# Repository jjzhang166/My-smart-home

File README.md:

# 目录结构说明

***

## server

服务器端程序(主要在Ubuntu12.04上测试, linux平台编译，运行都是没问题的)

使用方法请参考[编译和安装](http://git.oschina.net/xmeter/My-smart-home/wikis/%E7%BC%96%E8%AF%91%E5%92%8C%E5%AE%89%E8%A3%85)

友情提示go语言服务器版本请移步

http://git.oschina.net/ckrissun/smarthome-server

## dserver
 下一版开发的重点，服务器端由集中式变为分布式架构。
 
## tools 

提供些由于网络问题不好或者政策原因，软件包及调试工具

## opencv/facedect

人脸检测的源代码及例子(基于opencv + haar)

##  FastDFS

提供分布式云存储服务 ，感谢 Happy Fish / YuQing 的辛勤劳动

更多详细信息：http://www.csource.org/ 或者 googlecode有此项目

## iOS_Client、Android_Client、FirefoxOS_Client

各平台的客户端

* iOS客户端使用xcode5或以上打开即可

* Andriod客户端使用eclipse打开即可

 假如没有android开发环境， 可直接下载[已编译的Apk](http://git.oschina.net/xmeter/My-smart-home/blob/Client/Android_Client/bin/MyNode.apk)

* FirefoxOS客户端使用除记事本外的文本编辑器打开即可

**PS:现在客户端相关移至Client分支，确认无误后合并至master**

## ClientAPI、ClientWeb、ServerAPI、ServerWeb

http服务器代码，有问题请[提交Issue](http://git.oschina.net/xmeter/My-smart-home/issues/new)

**PS:现在Web相关移至Server分支，确认无误后合并至master**

## webhook

代码自动部署，持续集成

## hardware

硬件ardunio以及相关传感器的demo。(LM35，MQ2 MQ7 , W5100等)
     
* [硬件介绍](http://git.oschina.net/xmeter/My-smart-home/wikis/%E7%A1%AC%E4%BB%B6%E9%83%A8%E5%88%86%E4%BB%8B%E7%BB%8D)
       
***

> 更详细的说明，请移步 [WiKi](http://git.oschina.net/xmeter/My-smart-home/wikis/Home)

> 希望有新的小伙伴加入！

# 联系方式

***

### [李子](git.oschina.net/xmeter) liyongming1982@163.com _管理员_

服务器、硬件、Android Client

### [Rex](http://git.oschina.net/ckrissun) ckrissun@gmail.com _管理员_

服务器、协议、硬件

### [泷涯](http://git.oschina.net/sy) 896640547@qq.com _管理员_

数据库、Web、API
 
### [Pajoke](http://git.oschina.net/hell-prototypes) pajoke@163.com

硬件

更多Pajoke介绍请移步 ：  http://www.hellprototypes.com

### [siz](http://git.oschina.net/aliyuns) siz@sonwa.cn

iOS Client

### [fireman](http://git.oschina.net/colma) david_lxh@aliyun.com

特别感谢fireman，把Web服务移植到树莓派 (并写下文档供后来者参考)

### [Raythan](http://git.oschina.net/Raythan) raythandong@gmail.com

硬件

### [孤鹰](http://git.oschina.net/604217454) 604217454@qq.com

iOS Client

### [mzer](http://git.oschina.net/liduanjun) liduanjun@126.com

硬件及Web

# 感谢

***

   * 感谢xiangjm资助我200元人民币购买3D打印机
   * 感谢我老婆这个月多给了我点零花钱
   * 感谢3D淘宝店老板便宜了50元钱 http://3dprinter-diy.taobao.com/?spm=2013.1.0.0.donECP
   * ......

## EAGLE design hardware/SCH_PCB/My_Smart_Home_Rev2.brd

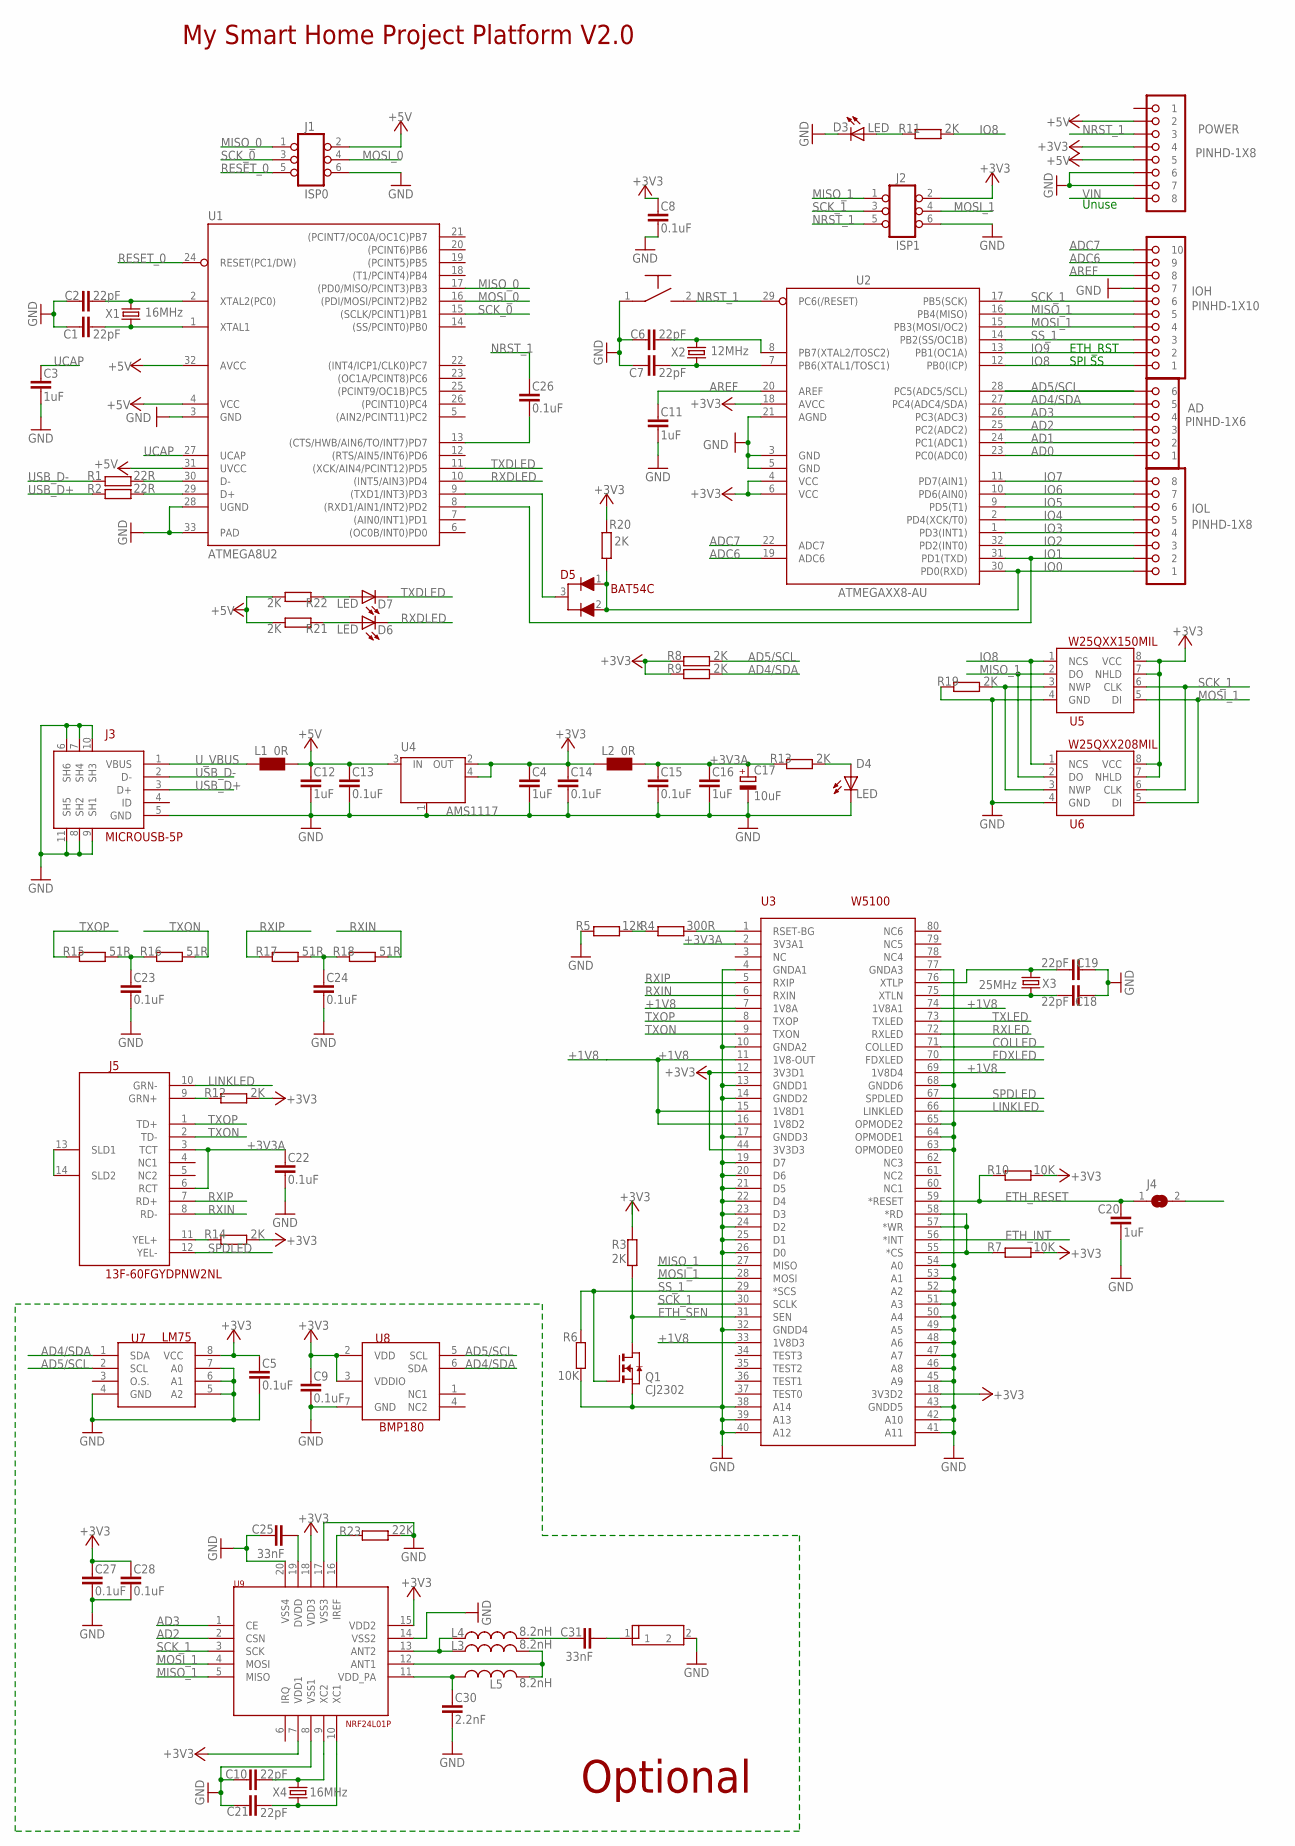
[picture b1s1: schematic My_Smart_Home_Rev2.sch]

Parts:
AD: PINHD-1X6; 1X06
ANT1: 2.4G_ANT1; 2.4G_PCB_ANT
C1, C2, C6, C7, C10, C18, C19, C21: 22pF; C0603
C3, C4, C11, C12, C16, C20: 1uF; C0603
C5, C8, C9, C13, C14, C15, C22, C23, C24, C26, C27, C28: 0.1uF; C0603
C17: 10uF; C0805
C25, C31: 33nF; C0603
C30: 2.2nF; C0603
D3, D4, D6, D7: LED; LED0805
D5: BAT54C; SOT23
IOH: PINHD-1X10; 1X10
IOL: PINHD-1X8; 1X08
J1: ISP0; 2X03
J2: ISP1; 2X03
J3: MICROUSB-5P; MICROUSB-5P-SMD
J4: JUMPER; SOLDER_JUMPER
J5: 13F-60FGYDPNW2NL
L1, L2: 0R; R0603
L3, L4, L5: 8.2nH; R0603
POWER: PINHD-1X8; 1X08
Q1: CJ2302; SOT23
R1, R2: 22R; R0603
R3, R8, R9, R11, R12, R13, R14, R19, R20, R21, R22: 2K; R0603
R4: 300R; R0603
R5: 12K; R0603
R6, R7, R10: 10K; R0603
R15, R16, R17, R18: 51R; R0603
R23: 22K; R0603
SW2: SW-2; SW-2P-SMD
U1: ATMEGA8U2; MLF32
U2: ATMEGAXX8-AU; TQFP32-08
U3: W5100; SQFP-S-10X10-80
U4: AMS1117; SOT223
U5: W25QXX150MIL; 8S1
U6: W25QXX208MIL; 8S2
U7: LM75; 8S1
U8: BMP180; LGA-7P
U9: NRF24L01P; QFN20
X1, X4: 16MHz; HC49UP
X2: 12MHz; HC49UP
X3: 25MHz; HC49UP

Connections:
+1V8: U3.7 (1V8A), U3.11 (1V8-OUT), U3.15 (1V8D1), U3.16 (1V8D2), U3.33 (1V8D3), U3.69 (1V8D4), U3.74 (1V8A1)
+3V3: C4.2, C5.2, C8.2, C9.2, C14.2, C27.2, C28.2, J2.2, L2.1, POWER.4, R3.2, R7.2, R8.2, R9.2, R10.2, R12.1, R14.1, R20.2, U2.4 (VCC), U2.6 (VCC), U2.18 (AVCC), U3.12 (3V3D1), U3.18 (3V3D2), U3.44 (3V3D3), U4.2 (OUT), U4.4 (OUT), U5.7 (NHLD), U5.8 (VCC), U6.7 (NHLD), U6.8 (VCC), U7.8 (VCC), U8.2 (VDD), U8.3 (VDDIO), U9.7 (VDD1), U9.15 (VDD2), U9.18 (VDD3)
+3V3A: C15.2, C16.2, C17.1 (+), C22.2, J5.3 (TCT), J5.6 (RCT), L2.2, R13.2, U3.2 (3V3A1)
+5V: C12.2, C13.2, J1.2, L1.2, POWER.2, POWER.5, R21.1, R22.1, U1.4 (VCC), U1.31 (UVCC), U1.32 (AVCC), U4.3 (IN)
AD0: AD.1, U2.23 (PC0(ADC0))
AD1: AD.2, U2.24 (PC1(ADC1))
AD2: AD.3, U2.25 (PC2(ADC2)), U9.2 (CSN)
AD3: AD.4, U2.26 (PC3(ADC3)), U9.1 (CE)
AD4/SDA: AD.5, R9.1, U2.27 (PC4(ADC4/SDA)), U7.1 (SDA), U8.6 (SDA)
AD5/SCL: AD.6, R8.1, U2.28 (PC5(ADC5/SCL)), U7.2 (SCL), U8.5 (SCL)
ADC6: IOH.9, U2.19 (ADC6)
ADC7: IOH.10, U2.22 (ADC7)
AREF: C11.2, IOH.8, U2.20 (AREF)
COLLED: U3.71 (COLLED)
ETH_INT: U3.56 (*INT)
ETH_RESET: C20.2, J4.1, R10.1, U3.59 (*RESET)
ETH_SEN: Q1.3 (D), R3.1, U3.31 (SEN)
FDXLED: U3.70 (FDXLED)
GND: ANT1.2, C1.1, C2.1, C3.1, C4.1, C5.1, C6.1, C7.1, C8.1, C9.1, C10.1, C11.1, C12.1, C13.1, C14.1, C15.1, C16.1, C17.2 (-), C18.1, C19.1, C20.1, C21.1, C22.1, C23.1, C24.1, C25.2, C27.1, C28.1, C30.1, D3.C, D4.C, IOH.7, J1.6, J2.6, J3.5 (GND), J3.6 (SH6), J3.7 (SH4), J3.8 (SH2), J3.9 (SH1), J3.10 (SH3), J3.11 (SH5), POWER.6, POWER.7, Q1.2 (S), R5.1, R6.1, R19.2, R23.1, SW2.1, U1.3 (GND), U1.28 (UGND), U1.33 (PAD), U2.3 (GND), U2.5 (GND), U2.21 (AGND), U3.4 (GNDA1), U3.10 (GNDA2), U3.13 (GNDD1), U3.14 (GNDD2), U3.17 (GNDD3), U3.19 (D7), U3.20 (D6), U3.21 (D5), U3.22 (D4), U3.23 (D3), U3.24 (D2), U3.25 (D1), U3.26 (D0), U3.32 (GNDD4), U3.38 (A14), U3.39 (A13), U3.40 (A12), U3.41 (A11), U3.42 (A10), U3.43 (GNDD5), U3.45 (A9), U3.46 (A8), U3.47 (A7), U3.48 (A6), U3.49 (A5), U3.50 (A4), U3.51 (A3), U3.52 (A2), U3.53 (A1), U3.54 (A0), U3.63 (OPMODE0), U3.64 (OPMODE1), U3.65 (OPMODE2), U3.68 (GNDD6), U3.77 (GNDA3), U4.1 (GND/ADJ), U5.4 (GND), U6.4 (GND), U7.4 (GND), U7.5 (A2), U7.6 (A1), U7.7 (A0), U8.7 (GND), U9.8 (VSS1), U9.14 (VSS2), U9.17 (VSS3), U9.20 (VSS4)
IO0: D5.1, D5.2, IOL.1, R20.1, U2.30 (PD0(RXD))
IO1: IOL.2, U1.8 ((RXD1/AIN1/INT2)PD2), U2.31 (PD1(TXD))
IO2: IOL.3, U2.32 (PD2(INT0))
IO3: IOL.4, U2.1 (PD3(INT1))
IO4: IOL.5, U2.2 (PD4(XCK/T0))
IO5: IOL.6, U2.9 (PD5(T1))
IO6: IOL.7, U2.10 (PD6(AIN0))
IO7: IOL.8, U2.11 (PD7(AIN1))
IO8: IOH.1, R11.1, U2.12 (PB0(ICP)), U5.1 (NCS), U6.1 (NCS)
IO9: IOH.2, J4.2, U2.13 (PB1(OC1A))
LINKLED: J5.10 (GRN-), U3.66 (LINKLED)
MISO_0: J1.1, U1.17 ((PD0/MISO/PCINT3)PB3)
MISO_1: IOH.5, J2.1, U2.16 (PB4(MISO)), U3.27 (MISO), U5.2 (DO), U6.2 (DO), U9.5 (MISO)
MOSI_0: J1.4, U1.16 ((PDI/MOSI/PCINT2)PB2)
MOSI_1: IOH.4, J2.4, U2.15 (PB3(MOSI/OC2)), U3.28 (MOSI), U5.5 (DI), U6.5 (DI), U9.4 (MOSI)
unnamed: C2.2, U1.2 (XTAL2(PC0)), X1.2
unnamed: C1.2, U1.1 (XTAL1), X1.1
unnamed: C18.2, U3.75 (XTLN), X3.2
unnamed: R7.1, U3.55 (*CS), U3.57 (*WR), U3.58 (*RD)
unnamed: C19.2, U3.76 (XTLP), X3.1
unnamed: C10.2, U9.9 (XC2), X4.2
unnamed: D5.3, U1.9 ((TXD1/INT3)PD3)
unnamed: C26.1, U1.13 ((CTS/HWB/AIN6/TO/INT7)PD7)
unnamed: R1.2, U1.30 (D-)
unnamed: D7.A, R22.2
unnamed: R2.2, U1.29 (D+)
unnamed: C21.2, U9.10 (XC1), X4.1
unnamed: L3.1, L4.1, U9.13 (ANT2)
unnamed: D4.A, R13.1
unnamed: D3.A, R11.2
unnamed: C6.2, U2.8 (PB7(XTAL2/TOSC2)), X2.2
unnamed: C7.2, U2.7 (PB6(XTAL1/TOSC1)), X2.1
unnamed: R4.2, U3.1 (RSET-BG)
unnamed: R4.1, R5.2
unnamed: J5.11 (YEL+), R14.2
unnamed: J5.9 (GRN+), R12.2
unnamed: C23.2, R15.1, R16.2
unnamed: D6.A, R21.2
unnamed: R23.2, U9.16 (IREF)
unnamed: J5.13 (SLD1), J5.14 (SLD2)
unnamed: C25.1, U9.19 (DVDD)
unnamed: C24.2, R17.1, R18.2
unnamed: L3.2, L5.2, U9.12 (ANT1)
unnamed: C30.2, L5.1, U9.11 (VDD_PA)
unnamed: R19.1, U5.3 (NWP), U6.3 (NWP)
unnamed: ANT1.1, C31.1
unnamed: C31.2, L4.2
NRST_1: C26.2, J2.5, POWER.3, SW2.2, U2.29 (PC6(/RESET))
RESET_0: J1.5, U1.24 (RESET(PC1/DW))
RXDLED: D6.C, U1.10 ((INT5/AIN3)PD4)
RXIN: J5.8 (RD-), R18.1, U3.6 (RXIN)
RXIP: J5.7 (RD+), R17.2, U3.5 (RXIP)
RXLED: U3.72 (RXLED)
SCK_0: J1.3, U1.15 ((SCLK/PCINT1)PB1)
SCK_1: IOH.6, J2.3, U2.17 (PB5(SCK)), U3.30 (SCLK), U5.6 (CLK), U6.6 (CLK), U9.3 (SCK)
SPDLED: J5.12 (YEL-), U3.67 (SPDLED)
SS_1: IOH.3, Q1.1 (G), R6.2, U2.14 (PB2(SS/OC1B)), U3.29 (*SCS)
TXDLED: D7.C, U1.11 ((XCK/AIN4/PCINT12)PD5)
TXLED: U3.73 (TXLED)
TXON: J5.2 (TD-), R16.1, U3.9 (TXON)
TXOP: J5.1 (TD+), R15.2, U3.8 (TXOP)
UCAP: C3.2, U1.27 (UCAP)
USB_D+: J3.3 (D+), R2.1
USB_D-: J3.2 (D-), R1.1
U_VBUS: J3.1 (VBUS), L1.1
VIN: POWER.8

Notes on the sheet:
Unuse
SPI SS
ETH_RST
My Smart Home Project Platform V2.0
Optional

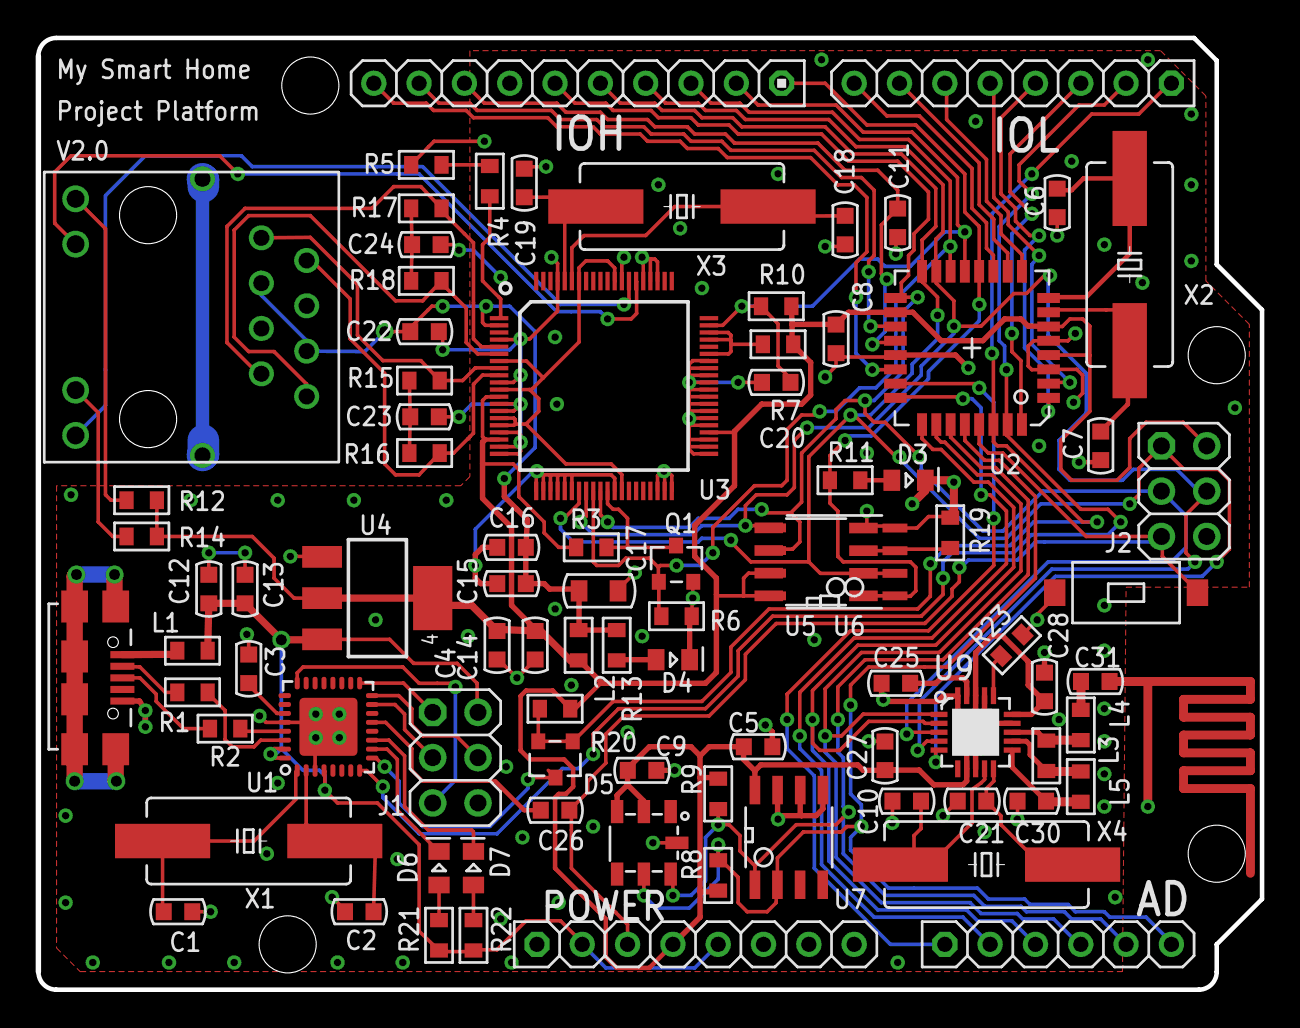
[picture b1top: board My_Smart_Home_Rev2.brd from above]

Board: 2 copper layers, 68.6 x 53.3 mm, 88 parts (1 on the bottom side), 79 nets.

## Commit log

2014-05-02 first version of my smart home server
2014-05-02 first version of android client
2014-05-02 add some debug or test scritp (python shell or php)
2014-05-02 first version of www (web) ,test it ie and firefox
2014-05-02 add readme
2014-05-03 add wiki link
2014-05-08 添加服务器端说明
2014-05-18 添加硬件介绍链接
2014-05-21 added mydebug, redislog instead of printf, added heartbeat and so on
2014-05-21 android client new protocol ,added light activity , add heart beat
2014-05-21 added some file
2014-05-21 hardware added MQ2 MQ7 sensor demo
2014-05-21 add hardware demo descript
2014-05-21 add second version of android client and server for compiler error
2014-05-21 added more file for server
2014-05-23 added light control demo wiht w5100
2014-05-29 Added .gitignore
2014-05-29 脚本移动
2014-05-29 dynamic add user , added server start script
2014-05-29 added two test development user in script
2014-05-29 mysql.php error
2014-05-31 添加小伙伴的邮箱
2014-06-01 removed *.o files improved chat send handling
2014-06-01 New iOS Project
2014-06-01 added chat message limitation to 70 length
2014-06-01 added iphone client development siz
2014-06-01 增加小伙伴
2014-06-02 added webhook
2014-06-03 add register feature , and modified some script
2014-06-03 change mode 777 for stop.sh
2014-06-03 change server port to 6379
2014-06-03 added log level for server crash
2014-06-03 added fake node client for test
2014-06-04 添加小伙伴
2014-06-05 欢迎小伙伴，掌声在哪里
2014-06-05 enable heart beat , and the value is 120s
2014-06-06 changed tcp-keepalive to 60s
2014-06-06 added debug info for heart beat
2014-06-06 for heart beat
2014-06-06 for avoid invalid client
2014-06-06 a socket cant login twice
2014-06-06 just for test
2014-06-07 fix webhook error
2014-06-07 fix tcp keepalive
2014-06-07 use heart beat , and delete redis native timeout
2014-06-07 show login fail reason
2014-06-07 put last android client MyNode.apk in bin
2014-06-07 修改android client 说明
2014-06-13 improved server compiling script
2014-06-13 fix server Makefile install error
2014-06-14 removed unused redis-related uitls
2014-06-18 added polarssl-havege algorithm library for register random generator
2014-06-18 fix havege library missing file && add test example
2014-06-19 added havege library compiling
2014-06-26 fix Broadcast Receiver leak
2014-06-26 support speech recognize
2014-06-28 添加感谢
2014-07-01 support on to air update
2014-07-01 fix ota bug check version.txt
2014-07-08 added restful api for first version use beego and go language
2014-07-08 added go beego gomysqldriver tools for restful api
2014-07-08 added restful
2014-07-08 go support 64 os
2014-07-09 show login status
2014-07-09 update version number for online update
2014-07-09 update android client apk
2014-07-09 changed go project structure
2014-07-11 restful: don't always open/close mysql db
2014-07-11 added models module
2014-07-13 close rows to free sql connection && write http header when errors issued.
2014-07-14 add restful tools
2014-07-16 added a company host page
2014-07-19 modified some ui , and fix some socket issue etc
2014-07-21 add a wizard for new user , and fixed online update bug ,etc
2014-07-29 added light activity , color pick ,time date pick etc
2014-08-01 add ipod style wheel
2014-08-02 我只是改了一下README.md
2014-08-02 把自己加进了小伙伴名单里
2014-08-02 热烈欢迎泷涯到来
2014-08-02 好吧我多打了个s
2014-08-02 将web分支的内容提交至主分支
2014-08-02 放这么大的东西不好 = =
2014-08-02 美化了一下README.md
2014-08-02 README.md
2014-08-04 项目的发展是大家努力贡献的结构 * 项目的首页出现大家的联系方式，是我们自己对自己的一个肯定
2014-08-04 tools 说明
2014-08-05 开源协议更改为MPL2.0协议
2014-08-05 手动合并web分支到server分支
2014-08-05 support protocol2.0 and usercase and some test script
2014-08-05 mysql drop table for test
2014-08-06 fixed mysql script bug and change table name from alluser to user
2014-08-06 change protocol from chat to user
2014-08-07 fix some protocol2.0 bug
2014-08-07 for web api and fix some protocol2.0 bug
2014-08-08 修复一个授权Bug
2014-08-08 新增注册网页
2014-08-09 API独立于Web开发
2014-08-09 markdown写错了
2014-08-09 修复几个Bug
2014-08-09 添加登录的WebAPI
2014-08-09 修复一个数据库类的Bug
2014-08-09 修复一个登录API的Bug
2014-08-09 修复一个Bug
2014-08-09 修复在线环境Bug
2014-08-09 修复一个数据库Bug
2014-08-09 修复一个文档错误和另外几处Bug
2014-08-10 修改目录名称
2014-08-10 修复重写规则
2014-08-10 提交Server基础
2014-08-10 新增注册API
2014-08-16 修复几个Bug，移除Client端的注册API
2014-08-16 新增SSDB
2014-08-16 更改为新的数据表，重写Auth算法
2014-08-16 测试API页面
2014-08-16 login的一个Bug
2014-08-16 完善文档
2014-08-16 新增API：myInfo
2014-08-16 少提交了一个东西
2014-08-16 新增API：获取所有节点组
2014-08-18 因数据库设计变动，Web端随之变动
2014-08-18 同步分支Server和Master
2014-08-18 我是搬运工
2014-08-18 修改目录结构说明
2014-08-18 markdown
2014-08-18 删除debug_script
2014-08-20 新增API：获取某一节点组下的所有节点
2014-08-20 修改节点相关数据库
2014-08-20 修改数据库结构
2014-08-20 API改变为获取节点组信息
2014-08-20 忘了修改一个地方了，。。。。
2014-08-21 go语言服务器
2014-08-26 hardware light support prototol 2.0
2014-08-31 face dect first version base on opencv for smart home alarm and etc
2014-08-31 face dect
2014-09-04 added fastDFS verson 1.14 ths YuQing
2014-09-04 提供分布式云存储服务
2014-09-05 添加FoosoUI组件（版本：Beta 0.4）
2014-09-06 php连接控制程序（测试中）
2014-09-13 新增获取节点信息的API，修复权限验证Bug
2014-09-13 修复语法错误
2014-09-22 新增大量API
2014-10-15 improve sql schema
2014-10-20 调整hardware内部的目录结构，添加硬件原理图，版本：Alpha1
2014-10-27 Update sch and add PCB file, HW Version: Alpha2
2014-11-07 Bootloader and 3 firmware creat, need more test
2014-11-10 Add a firmware for network test
2014-11-10 Update Hellduino_SystemDataConfig firmware
2015-03-17 support weixin user communication
2015-05-07 Fix Hellduino V2.0 HW bugs, HW version update to V2.1
2015-05-25 initial monitor of facedetect
2015-10-10 just for distrubuted server initial version
2015-10-10 更新dserver部分
